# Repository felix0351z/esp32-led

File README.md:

# LED Adapter circuit for the ESP32 Dev Kit C V4 NodeMCU

This project is circuit for the esp32 NodeMCU microcontroller to give the possibility to easily add an addressable led strip, like the ws2812b or the sk6812. The circuit will be powered via a USB-C connector and can be plugged onto the ESP32.

## How does it work?

The esp32 is connected to the power supply of the circuit and the addressable pin for the strip. The signal will then be level-shifted from 3.3V to 5V. On the top of the circuit is the connection for the 3-pin connector to plug in your strip.

## How to use

### Editing

This project was created with KiCad 5.1. If you wish to edit the schematic or footprint install KiCad and clone this repository.
```bash 
git clone https://github.com/felix0351z/esp32-led
```

After that you need to import the necessary footprints which kicad doesn't ship automatically.
I used 3 external footprints for the [USB-Connector](https://www.snapeda.com/parts/USB4125-GF-A/Global%20Connector%20Technology/view-part/), 
the [ESP32 NodeMCU](https://www.snapeda.com/parts/ESP32-DEVKITC-32D/Espressif%20Systems/view-part/) board and the [level shifter](https://www.snapeda.com/parts/SN74AHCT125D/Texas%20Instruments/view-part/).

You can download the footprints on SnapEDA and import them to KiCad. If you have other pcb parts at home, you can change them of course.

### Ordering 

If you want to order a pcb you can select a manufacturer of your choice. I used [JLCPCB](https://jlcpcb.com/) for this. Upload the gerber files and go!

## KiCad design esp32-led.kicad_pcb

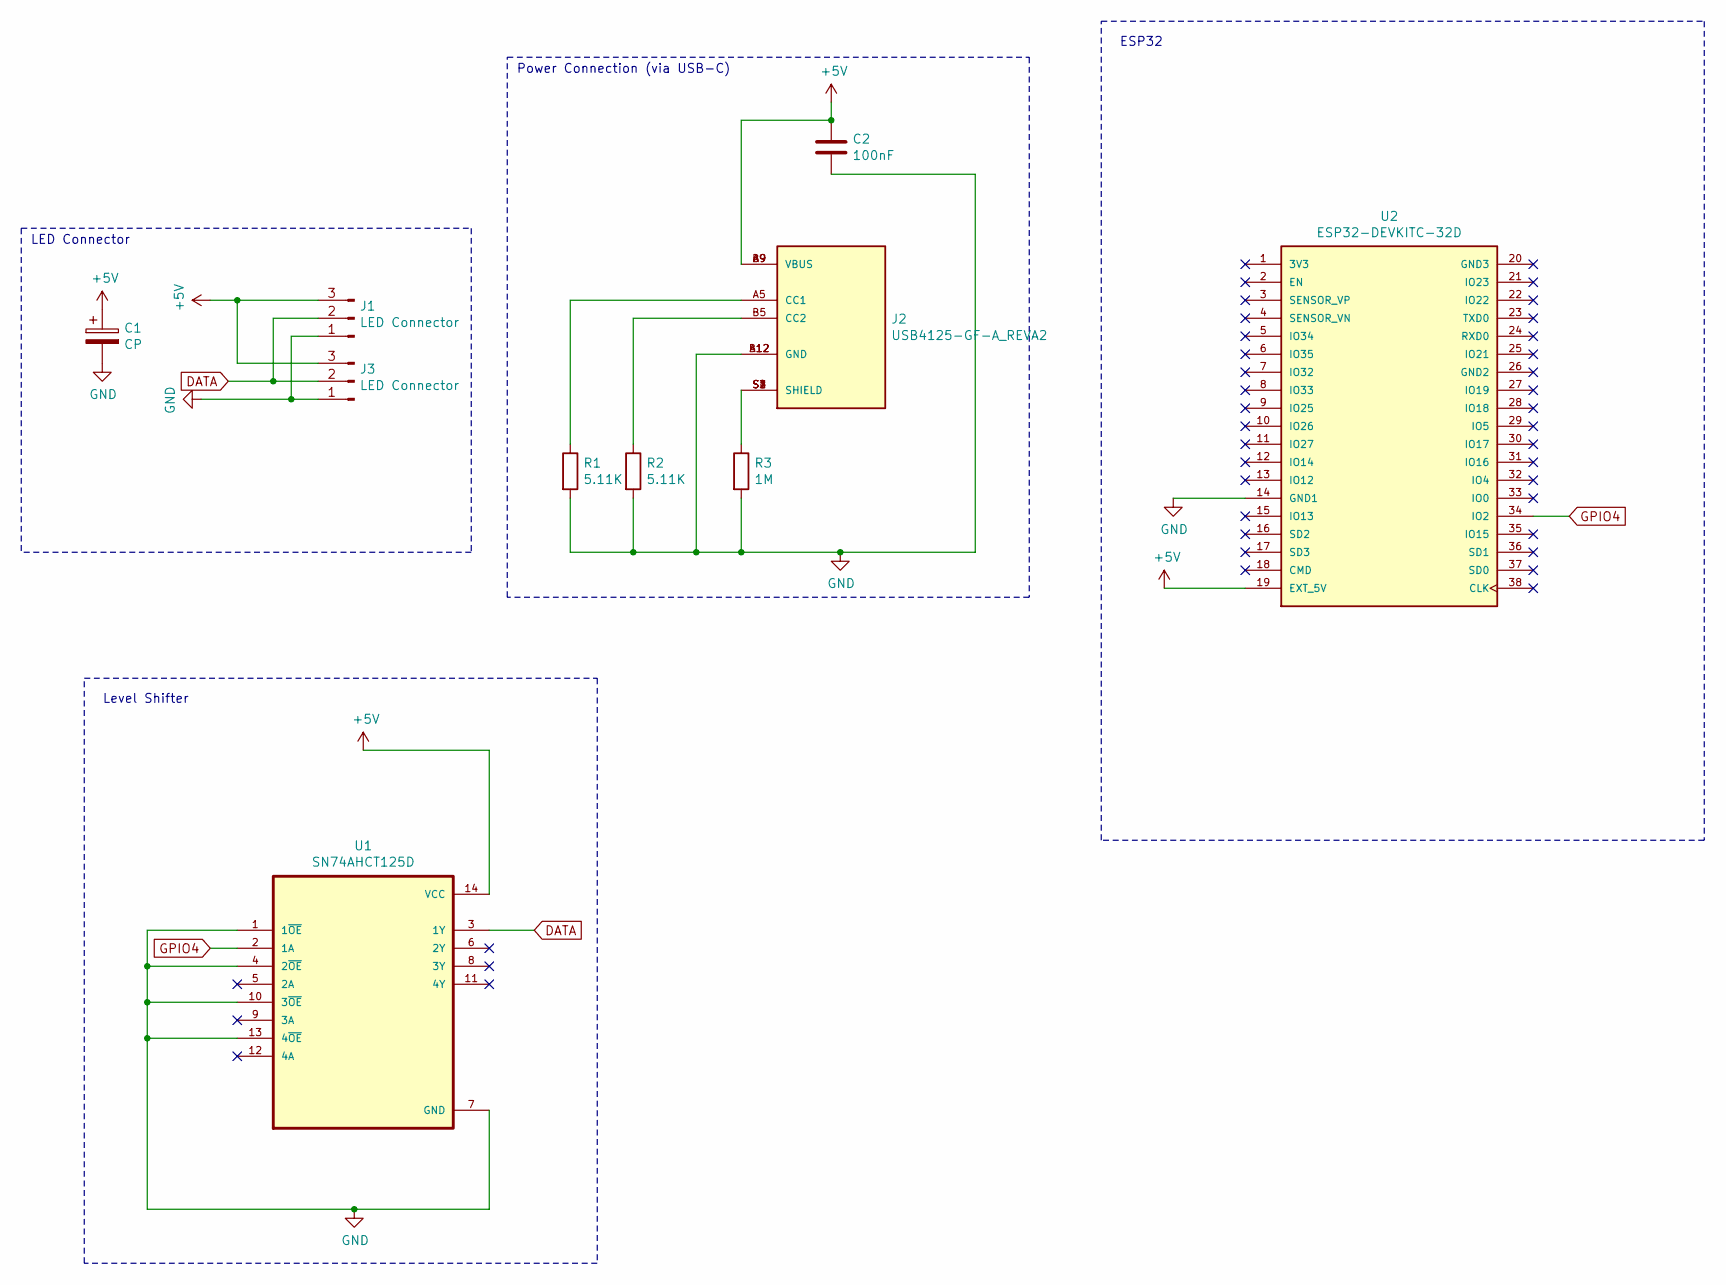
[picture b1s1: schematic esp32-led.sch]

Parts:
C1: CP; CP_Radial_D10.0mm_P5.00mm
C2: 100nF; C_0805_2012Metric_Pad1.18x1.45mm_HandSolder
J1, J3: LED Connector; PinHeader_1x03_P2.54mm_Vertical
J2: USB4125-GF-A_REVA2; GCT_USB4125-GF-A_REVA2; PARTREV Rev A2
R1, R2: 5.11K; R_0805_2012Metric_Pad1.20x1.40mm_HandSolder
R3: 1M; R_0805_2012Metric_Pad1.20x1.40mm_HandSolder
U1: SN74AHCT125D; SOIC127P600X175-14N
U2: ESP32-DEVKITC-32D; MODULE_ESP32-DEVKITC-32D; PARTREV 4

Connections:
+5V: C1.1, C2.1, J1.3, J2.A9 (VBUS), J2.B9 (VBUS), J3.3, U1.14 (VCC), U2.19 (EXT_5V)
DATA: J1.2, J3.2, U1.3 (1Y)
GND: C1.2, C2.2, J1.1, J2.A12 (GND), J2.B12 (GND), J3.1, R1.2, R2.2, R3.2, U1.1 (1~OE), U1.4 (2~OE), U1.7 (GND), U1.10 (3~OE), U1.13 (4~OE), U2.14 (GND1)
GPIO4: U1.2 (1A), U2.34 (IO2)
unnamed: J2.A5 (CC1), R1.1
unnamed: J2.B5 (CC2), R2.1
unnamed: J2.S1 (SHIELD), J2.S2 (SHIELD), J2.S3 (SHIELD), J2.S4 (SHIELD), R3.1

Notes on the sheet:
Power Connection (via USB-C)
ESP32
LED Connector
Level Shifter

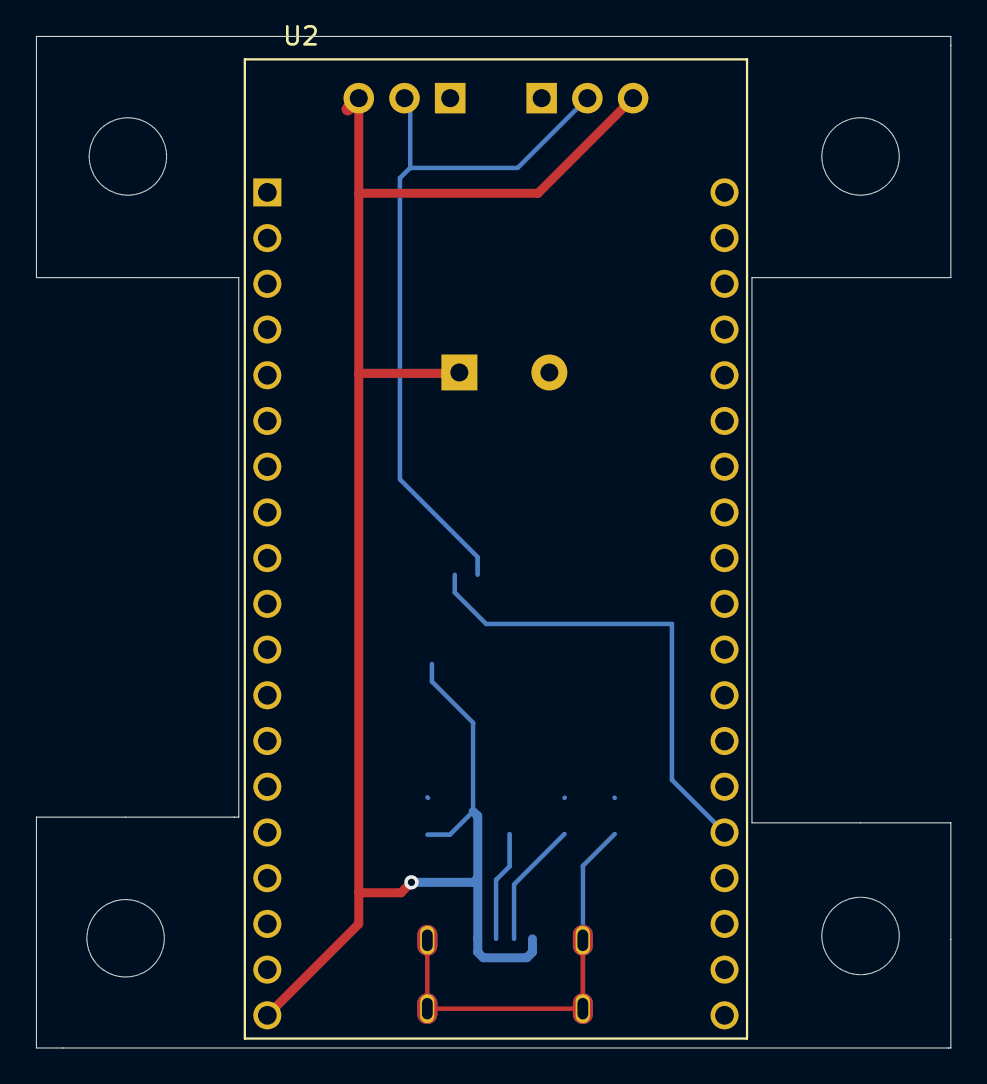
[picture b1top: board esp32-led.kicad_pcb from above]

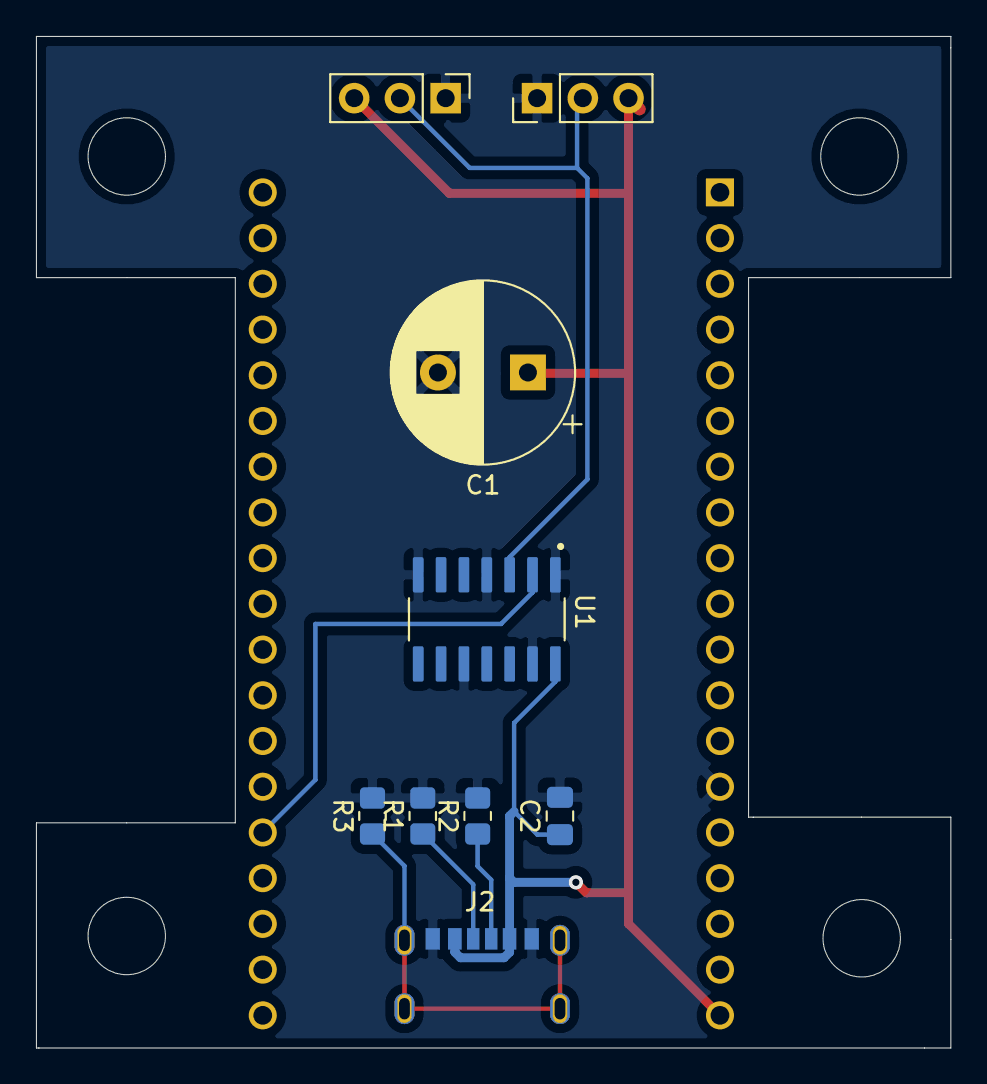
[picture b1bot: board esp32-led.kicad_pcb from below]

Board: 2 copper layers, 50.8 x 56.2 mm, 10 parts (9 on the bottom side), 7 nets.

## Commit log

2022-08-02 Added preview images
2022-08-03 Fixed issues, added gerber files
2022-08-03 Added barrel jack version
2022-08-20 Changed the wrong esp32 footprint
2022-08-20 Chamged wrong esp32 footprint
2023-07-16 Added README.md
